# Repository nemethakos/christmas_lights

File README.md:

# Animated Christmas Lights with Arduino.

Project description: http://fritzing.org/projects/christmas-lights

Christmas Lights in action: https://www.youtube.com/watch?v=RwZ6XnqKiA4

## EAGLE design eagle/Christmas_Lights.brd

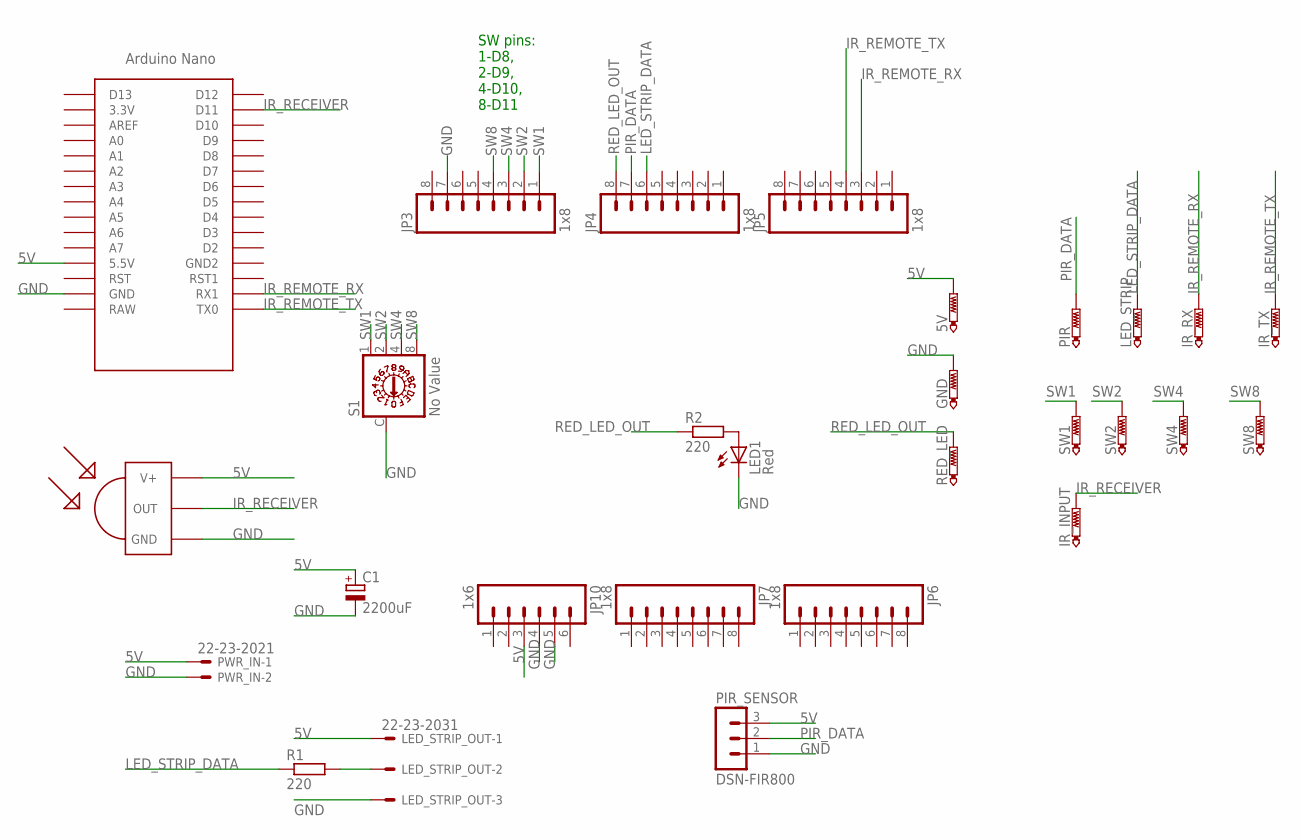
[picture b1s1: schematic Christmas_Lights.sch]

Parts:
5V: PTR1PAD1-13; P1-13
C1: 2200uF; E5-13
GND: PTR1PAD1-13; P1-13
IR_INPUT: PTR1PAD1-13; P1-13
IR_RX: PTR1PAD1-13; P1-13
IR_TX: PTR1PAD1-13; P1-13
JP3, JP4, JP5, JP6, JP7: 1x8; 1X08_LOCK
JP10: 1x6; 1X06_LOCK
LED1: Red; LED5MM
LED_STRIP: PTR1PAD1-13; P1-13
LED_STRIP_OUT: 22-23-2031
PIR: PTR1PAD1-13; P1-13
PIR_SENSOR: DSN-FIR800; MA03-1
PWR_IN: 22-23-2021
R1, R2: 220; 0204/7
RED_LED: PTR1PAD1-13; P1-13
S1: No Value; P103
SW1, SW2, SW4, SW8: PTR1PAD1-13; P1-13
TSOP31328: TSOP 31238; TSOP17XX
U$1: NANO

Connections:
5V: 5V.TP, C1.+, JP10.3, LED_STRIP_OUT.1, PIR_SENSOR.3, PWR_IN.1, TSOP31328.V+, U$1.5V (5.5V)
GND: C1.-, GND.TP, JP3.7, JP10.4, JP10.5, LED1.K (C), LED_STRIP_OUT.3, PIR_SENSOR.1, PWR_IN.2, S1.C, TSOP31328.GND, U$1.GND
IR_RECEIVER: IR_INPUT.TP, TSOP31328.OUT, U$1.D11
IR_REMOTE_RX: IR_RX.TP, JP5.3, U$1.RX1
IR_REMOTE_TX: IR_TX.TP, JP5.4, U$1.TX0
LED_STRIP_DATA: JP4.6, LED_STRIP.TP, R1.1
unnamed: LED_STRIP_OUT.2, R1.2
unnamed: LED1.A, R2.2
PIR_DATA: JP4.7, PIR.TP, PIR_SENSOR.2
RED_LED_OUT: JP4.8, R2.1, RED_LED.TP
SW1: JP3.1, S1.1, SW1.TP
SW2: JP3.2, S1.2, SW2.TP
SW4: JP3.3, S1.4, SW4.TP
SW8: JP3.4, S1.8, SW8.TP

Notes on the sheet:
SW pins: 1-D8, 2-D9, 4-D10, 8-D11

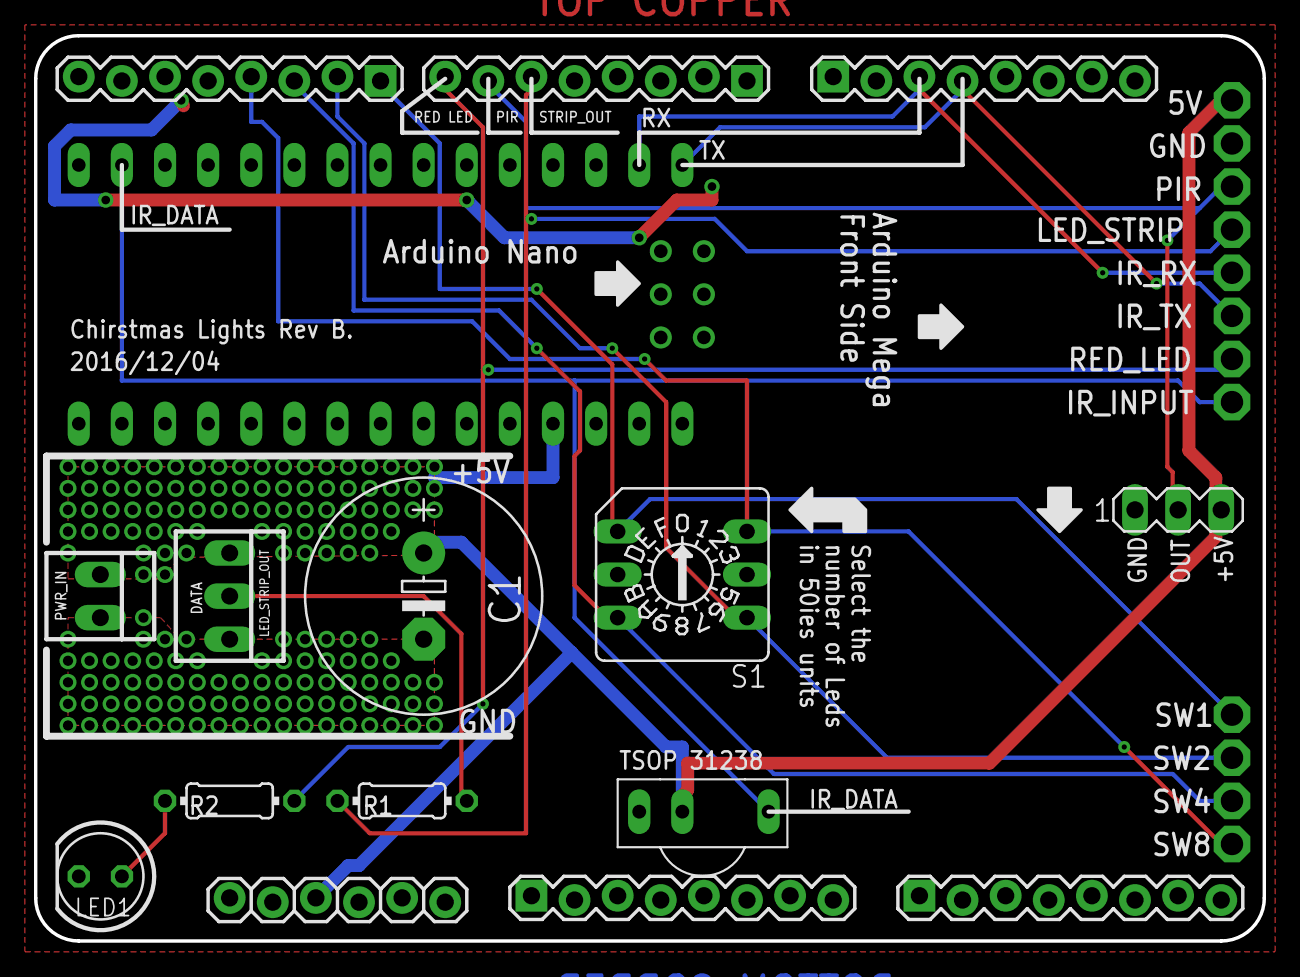
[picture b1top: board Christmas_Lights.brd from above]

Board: 2 copper layers, 72.4 x 53.3 mm, 28 parts (0 on the bottom side), 14 nets.

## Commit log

2018-07-08 Fritzing project site referenced, video added
2018-07-08 Youtube preview image added
2018-07-08 eagle, gerber and media files added
